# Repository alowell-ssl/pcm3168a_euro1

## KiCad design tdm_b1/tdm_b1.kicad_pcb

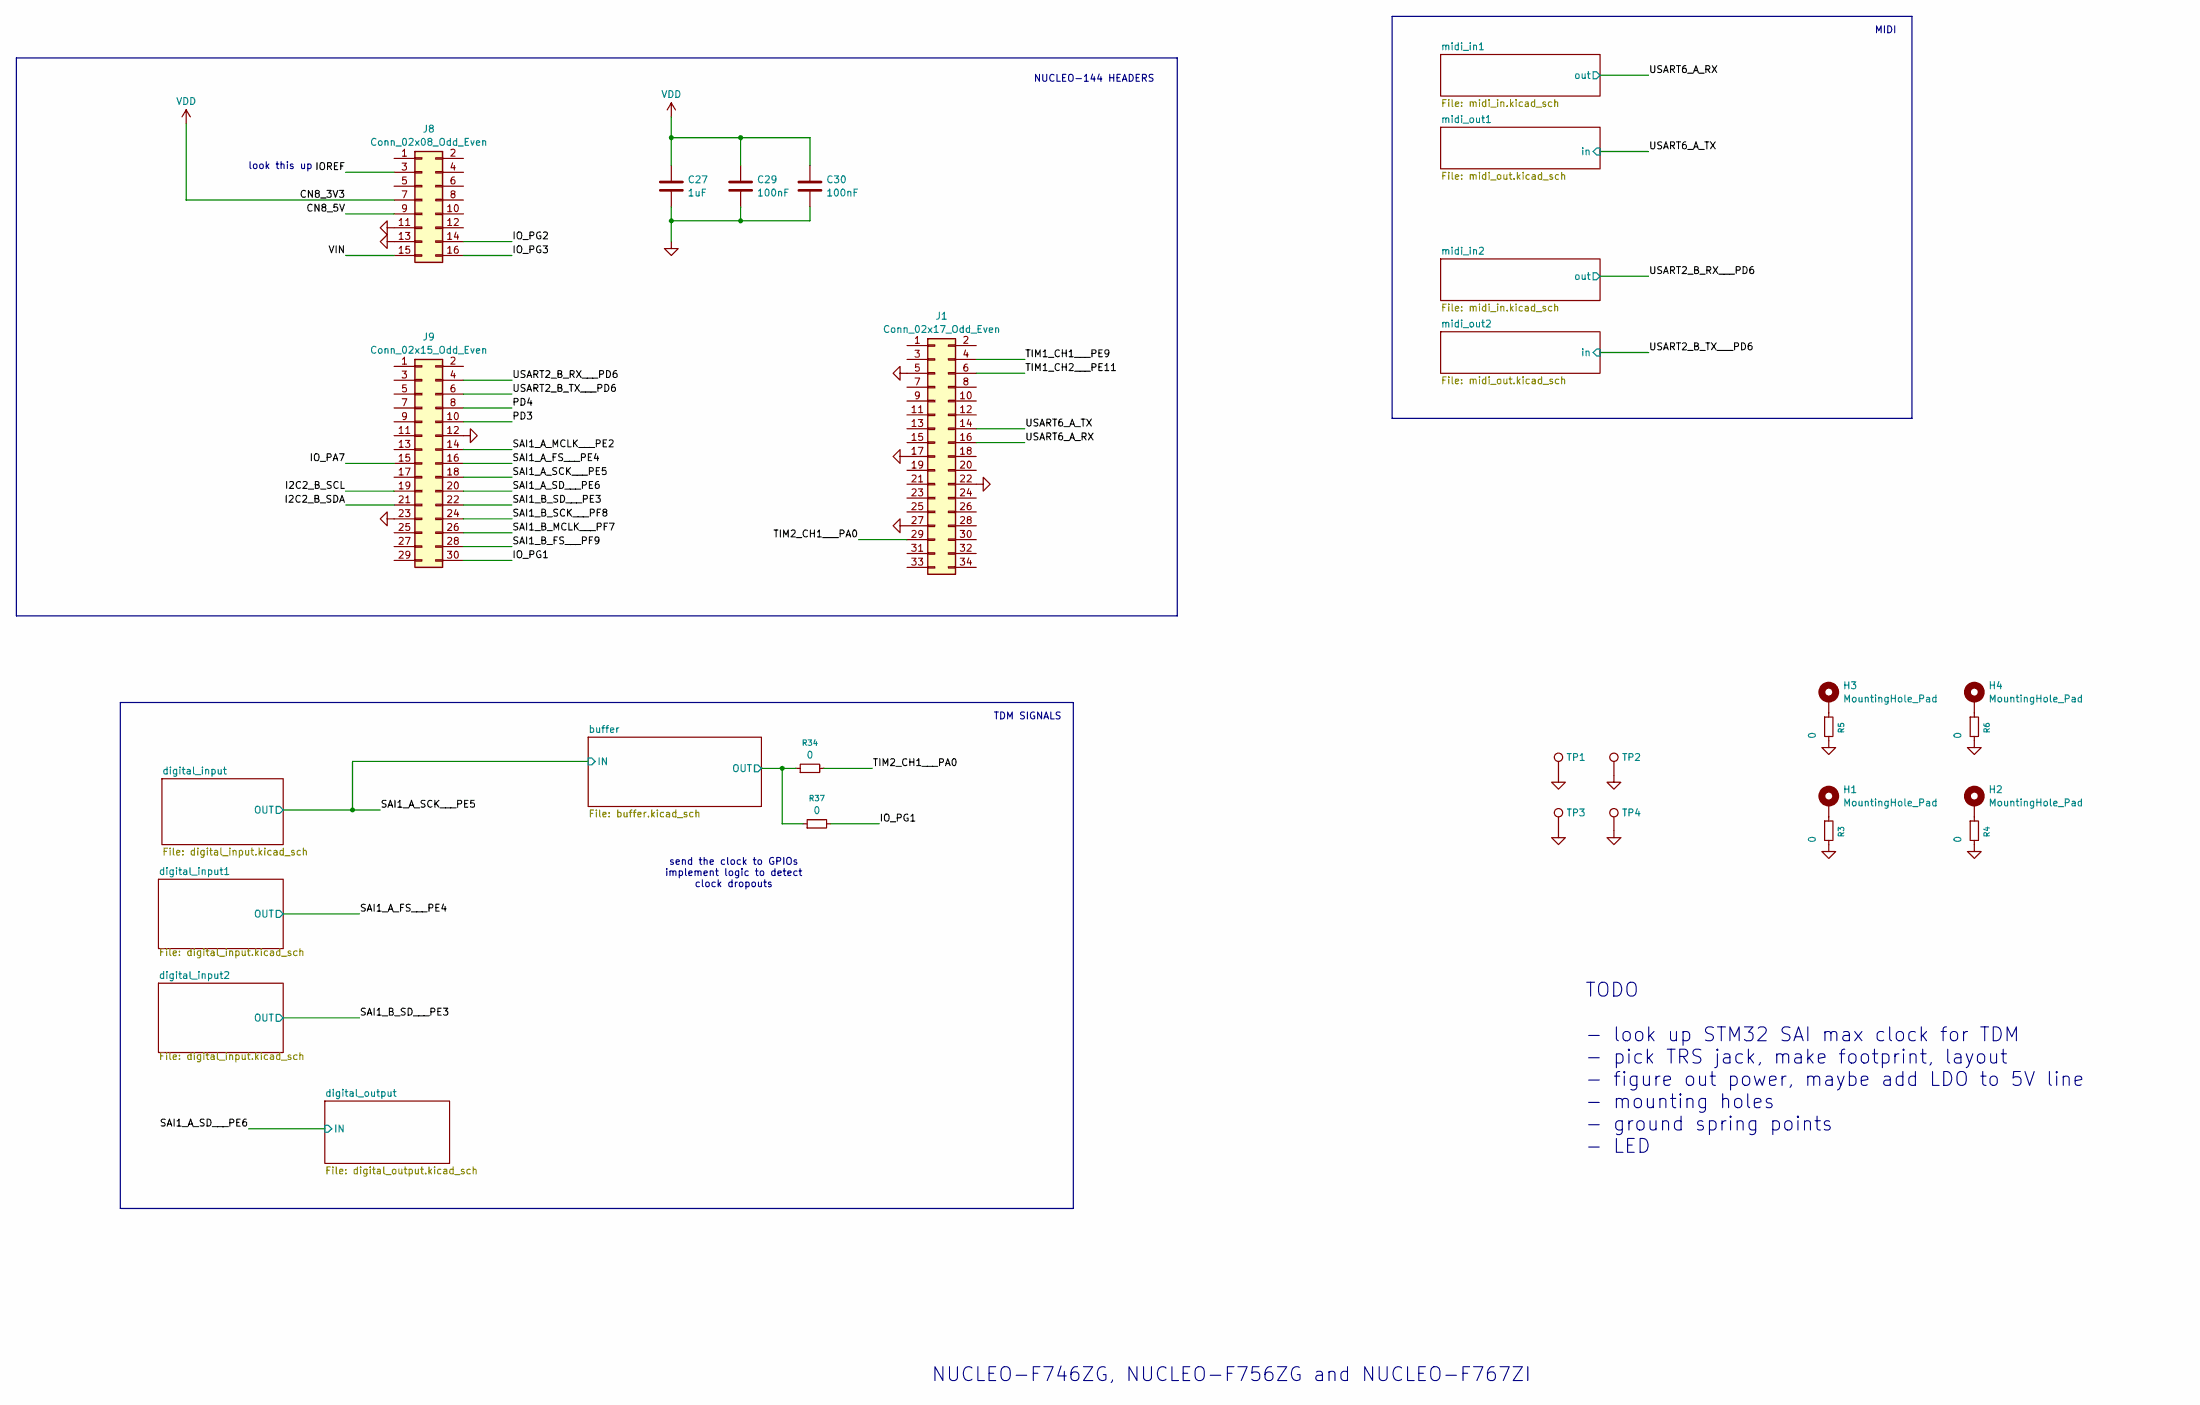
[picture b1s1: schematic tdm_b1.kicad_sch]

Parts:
C27: 1uF; C_0603_1608Metric
C29, C30: 100nF; C_0603_1608Metric
H1, H2, H3, H4: MountingHole_Pad; MountingHole_3.2mm_M3_DIN965_Pad
J1: Conn_02x17_Odd_Even; PinHeader_2x17_P2.54mm_Vertical
J8: Conn_02x08_Odd_Even; PinHeader_2x08_P2.54mm_Vertical
J9: Conn_02x15_Odd_Even; PinHeader_2x15_P2.54mm_Vertical
R3, R4, R5, R6, R34, R37: 0; R_0603_1608Metric
TP1, TP2, TP3, TP4: TestPoint; TestPoint_THTPad_D1.5mm_Drill0.7mm

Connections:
/CN8_5V: J8.9
/I2C2_B_SCL: J9.19
/I2C2_B_SDA: J9.21
/IOREF: J8.3
/IO_PA7: J9.15
/IO_PG1: J9.30, R37.2
/IO_PG2: J8.14
/IO_PG3: J8.16
/PD3: J9.10
/PD4: J9.8
/SAI1_A_FS___PE4: J9.16; also elsewhere on the board
/SAI1_A_MCLK___PE2: J9.14
/SAI1_A_SCK___PE5: J9.18; also elsewhere on the board
/SAI1_A_SD___PE6: J9.20; also elsewhere on the board
/SAI1_B_FS___PF9: J9.28
/SAI1_B_MCLK___PF7: J9.26
/SAI1_B_SCK___PF8: J9.24
/SAI1_B_SD___PE3: J9.22; also elsewhere on the board
/TIM1_CH1___PE9: J1.4
/TIM1_CH2___PE11: J1.6
/TIM2_CH1___PA0: J1.29, R34.2
/USART2_B_RX___PD6: J9.4; also elsewhere on the board
/USART2_B_TX___PD6: J9.6; also elsewhere on the board
/USART6_A_RX: J1.16; also elsewhere on the board
/USART6_A_TX: J1.14; also elsewhere on the board
/VIN: J8.15
/buffer/OUT: R34.1, R37.1; also elsewhere on the board
GND: C27.2, C29.2, C30.2, J1.5, J1.17, J1.22, J1.27, J8.11, J8.13, J9.12, J9.23, R3.2, R4.2, R5.2, R6.2, TP1.1, TP2.1, TP3.1, TP4.1; also elsewhere on the board
unnamed: H1.1, R3.1
unnamed: H2.1, R4.1
unnamed: H3.1, R5.1
unnamed: H4.1, R6.1
VDD: C27.1, C29.1, C30.1, J8.7; also elsewhere on the board

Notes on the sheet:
TDM SIGNALS
TODO - look up STM32 SAI max clock for TDM - pick TRS jack, make footprint, layout - figure out power, maybe add LDO to 5V line - mounting holes - ground spring points - LED
NUCLEO-144 HEADERS
look this up
send the clock to GPIOs implement logic to detect clock dropouts
NUCLEO-F746ZG, NUCLEO-F756ZG and NUCLEO-F767ZI
MIDI

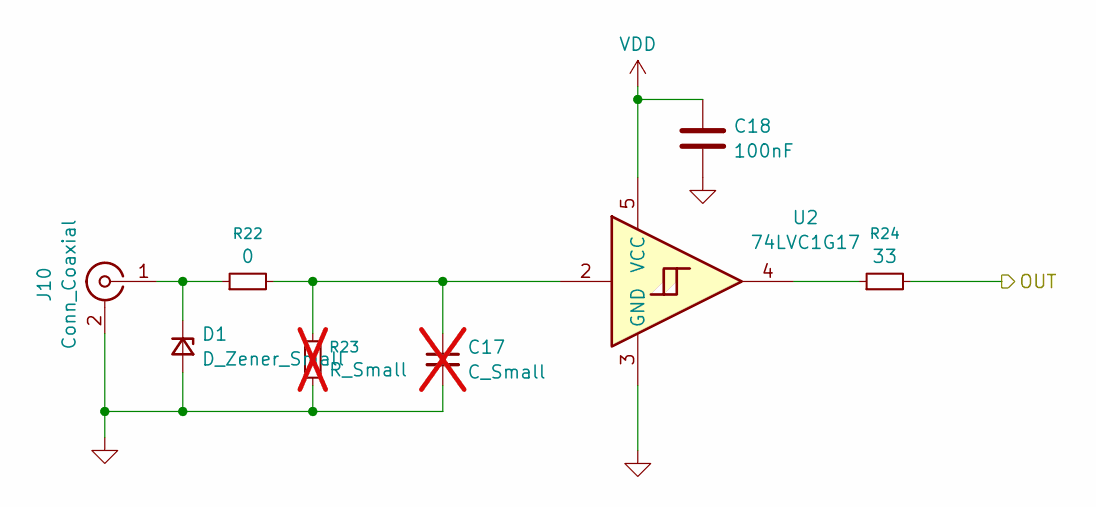
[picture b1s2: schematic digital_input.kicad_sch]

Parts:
C17: C_Small; C_0603_1608Metric; not fitted
C18: 100nF; C_0603_1608Metric
D1: D_Zener_Small; D_SOD-123F
J10: Conn_Coaxial; SMA_Amphenol_901-144_Vertical
R22: 0; R_0603_1608Metric
R23: R_Small; R_0603_1608Metric; not fitted
R24: 33; R_0603_1608Metric
U2: 74LVC1G17; SOT-23-5

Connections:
/SAI1_A_SCK___PE5: R24.2; also elsewhere on the board
GND: C17.2, C18.2, D1.2 (A), J10.2 (Ext), R23.1, U2.3 (GND); also elsewhere on the board
unnamed: C17.1, R22.2, R23.2, U2.2
unnamed: D1.1 (K), J10.1 (In), R22.1
unnamed: R24.1, U2.4
VDD: C18.1, U2.5 (VCC); also elsewhere on the board

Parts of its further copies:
C19, C21: C_Small; C_0603_1608Metric; not fitted
C20, C22: 100nF; C_0603_1608Metric
D2, D3: D_Zener_Small; D_SOD-123F
J11, J13: Conn_Coaxial; SMA_Amphenol_901-144_Vertical
R25, R28: 0; R_0603_1608Metric
R26, R29: R_Small; R_0603_1608Metric; not fitted
R27, R30: 33; R_0603_1608Metric
U3, U4: 74LVC1G17; SOT-23-5

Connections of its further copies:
/SAI1_A_FS___PE4: R27.2; also elsewhere on the board
/SAI1_B_SD___PE3: R30.2; also elsewhere on the board
GND: C19.2, C20.2, C21.2, C22.2, D2.2 (A), D3.2 (A), J11.2 (Ext), J13.2 (Ext), R26.1, R29.1, U3.3 (GND), U4.3 (GND); also elsewhere on the board
unnamed: C19.1, R25.2, R26.2, U3.2
unnamed: C21.1, R28.2, R29.2, U4.2
unnamed: D2.1 (K), J11.1 (In), R25.1
unnamed: D3.1 (K), J13.1 (In), R28.1
unnamed: R27.1, U3.4
unnamed: R30.1, U4.4
VDD: C20.1, C22.1, U3.5 (VCC), U4.5 (VCC); also elsewhere on the board

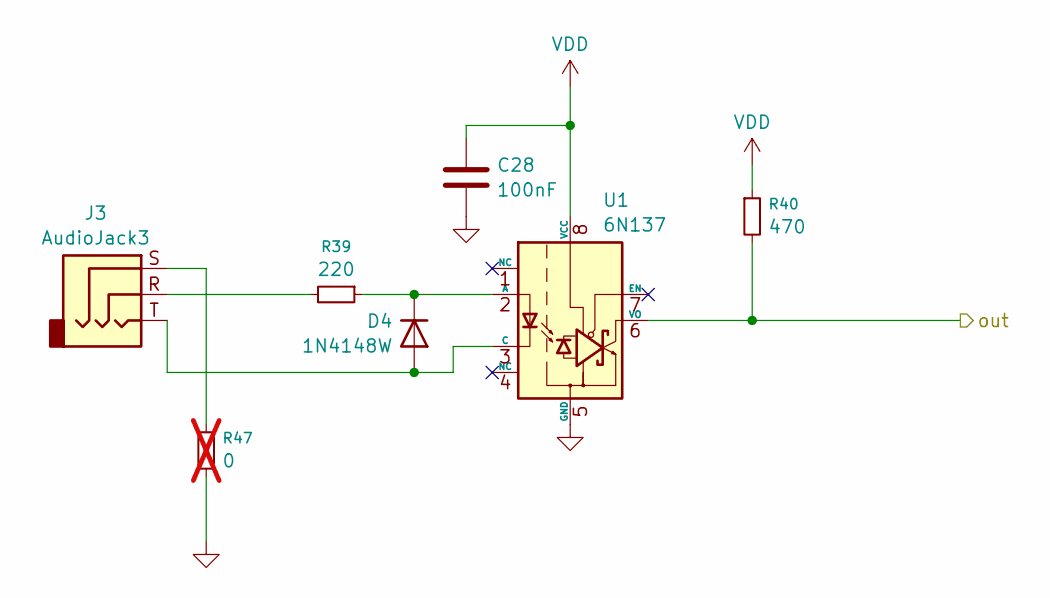
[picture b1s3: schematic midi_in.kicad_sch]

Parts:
C28: 100nF; C_0603_1608Metric
D4: 1N4148W; D_SOD-123
J3: AudioJack3; SJ1-3523N
R39: 220; R_0603_1608Metric
R40: 470; R_0603_1608Metric
R47: 0; R_0603_1608Metric; not fitted
U1: 6N137; DIP-8_W7.62mm

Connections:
/USART6_A_RX: R40.2, U1.6 (VO); also elsewhere on the board
GND: C28.2, R47.1, U1.5 (GND); also elsewhere on the board
unnamed: D4.2 (A), J3.T, U1.3 (C)
unnamed: D4.1 (K), R39.1, U1.2 (A)
unnamed: J3.R, R39.2
unnamed: J3.S, R47.2
VDD: C28.1, R40.1, U1.8 (VCC); also elsewhere on the board

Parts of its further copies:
C33: 100nF; C_0603_1608Metric
D5: 1N4148W; D_SOD-123
J5: AudioJack3; SJ1-3523N
R44: 220; R_0603_1608Metric
R45: 470; R_0603_1608Metric
R50: 0; R_0603_1608Metric; not fitted
U8: 6N137; DIP-8_W7.62mm

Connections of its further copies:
/USART2_B_RX___PD6: R45.2, U8.6 (VO); also elsewhere on the board
GND: C33.2, R50.1, U8.5 (GND); also elsewhere on the board
unnamed: D5.2 (A), J5.T, U8.3 (C)
unnamed: D5.1 (K), R44.1, U8.2 (A)
unnamed: J5.R, R44.2
unnamed: J5.S, R50.2
VDD: C33.1, R45.1, U8.8 (VCC); also elsewhere on the board

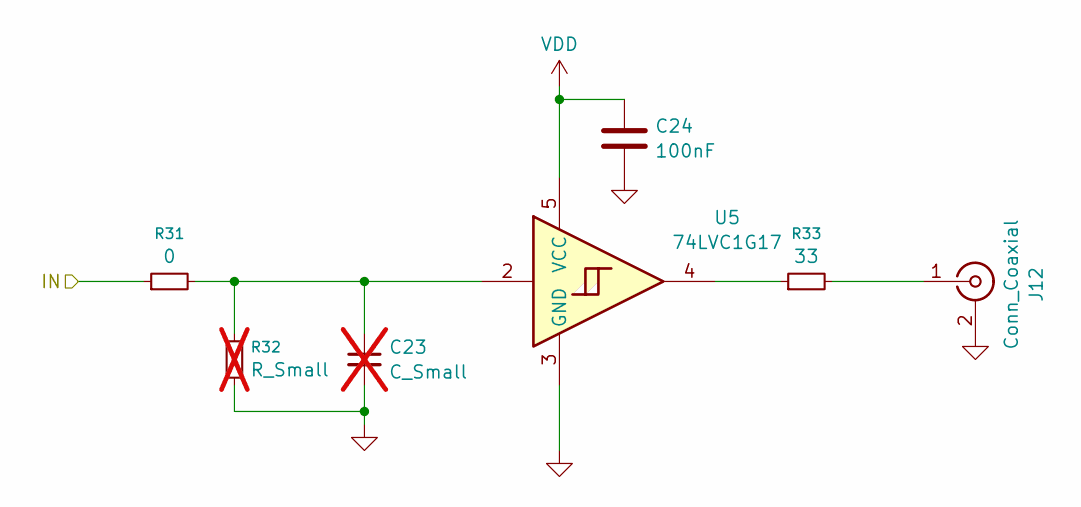
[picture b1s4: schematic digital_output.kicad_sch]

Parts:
C23: C_Small; C_0603_1608Metric; not fitted
C24: 100nF; C_0603_1608Metric
J12: Conn_Coaxial; SMA_Amphenol_901-144_Vertical
R31: 0; R_0603_1608Metric
R32: R_Small; R_0603_1608Metric; not fitted
R33: 33; R_0603_1608Metric
U5: 74LVC1G17; SOT-23-5

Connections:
/SAI1_A_SD___PE6: R31.1; also elsewhere on the board
GND: C23.2, C24.2, J12.2 (Ext), R32.1, U5.3 (GND); also elsewhere on the board
unnamed: C23.1, R31.2, R32.2, U5.2
unnamed: J12.1 (In), R33.2
unnamed: R33.1, U5.4
VDD: C24.1, U5.5 (VCC); also elsewhere on the board

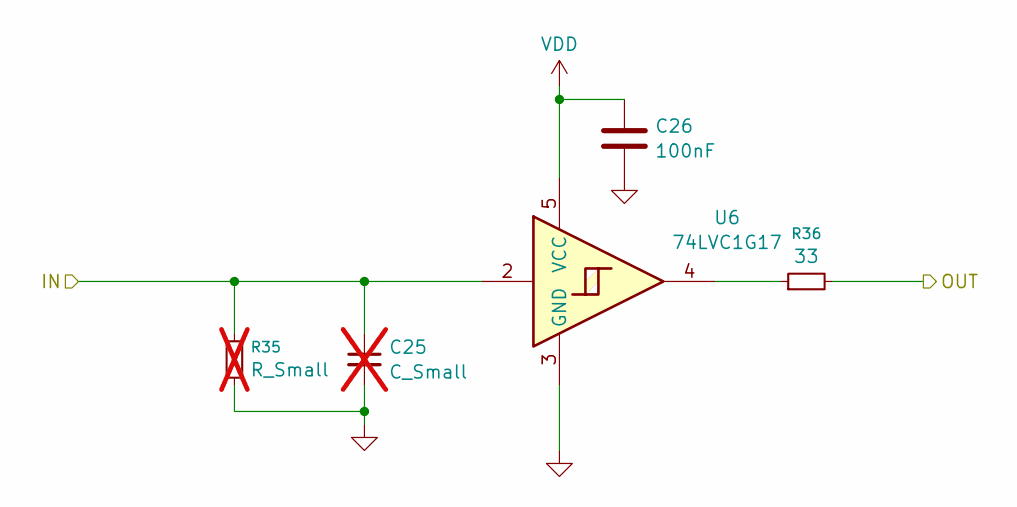
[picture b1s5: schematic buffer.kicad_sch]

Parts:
C25: C_Small; C_0603_1608Metric; not fitted
C26: 100nF; C_0603_1608Metric
R35: R_Small; R_0603_1608Metric; not fitted
R36: 33; R_0603_1608Metric
U6: 74LVC1G17; SOT-23-5

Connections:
/SAI1_A_SCK___PE5: C25.1, R35.2, U6.2; also elsewhere on the board
/buffer/OUT: R36.2; also elsewhere on the board
GND: C25.2, C26.2, R35.1, U6.3 (GND); also elsewhere on the board
unnamed: R36.1, U6.4
VDD: C26.1, U6.5 (VCC); also elsewhere on the board

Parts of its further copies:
C31, C34: C_Small; C_0603_1608Metric; not fitted
C32, C35: 100nF; C_0603_1608Metric
R41, R46: R_Small; R_0603_1608Metric; not fitted
R42, R51: 33; R_0603_1608Metric
U7, U9: 74LVC1G17; SOT-23-5

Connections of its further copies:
/USART2_B_TX___PD6: C34.1, R46.2, U9.2; also elsewhere on the board
/USART6_A_TX: C31.1, R41.2, U7.2; also elsewhere on the board
/midi_out1/MIDI_OUT: R42.2; also elsewhere on the board
/midi_out2/MIDI_OUT: R51.2; also elsewhere on the board
GND: C31.2, C32.2, C34.2, C35.2, R41.1, R46.1, U7.3 (GND), U9.3 (GND); also elsewhere on the board
unnamed: R42.1, U7.4
unnamed: R51.1, U9.4
VDD: C32.1, C35.1, U7.5 (VCC), U9.5 (VCC); also elsewhere on the board

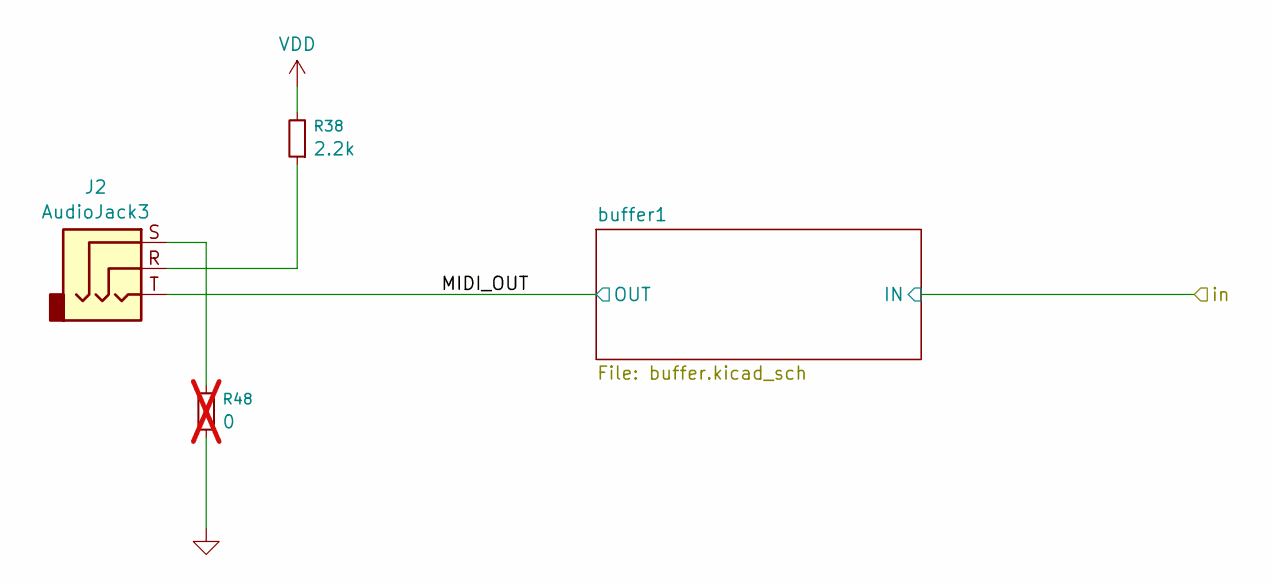
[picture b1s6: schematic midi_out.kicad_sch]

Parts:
J2: AudioJack3; SJ1-3523N
R38: 2.2k; R_0603_1608Metric
R48: 0; R_0603_1608Metric; not fitted

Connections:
/midi_out1/MIDI_OUT: J2.T; also elsewhere on the board
GND: R48.1; also elsewhere on the board
unnamed: J2.R, R38.1
unnamed: J2.S, R48.2
VDD: R38.2; also elsewhere on the board

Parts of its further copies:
J4: AudioJack3; SJ1-3523N
R43: 2.2k; R_0603_1608Metric
R49: 0; R_0603_1608Metric; not fitted

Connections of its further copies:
/midi_out2/MIDI_OUT: J4.T; also elsewhere on the board
GND: R49.1; also elsewhere on the board
unnamed: J4.R, R43.1
unnamed: J4.S, R49.2
VDD: R43.2; also elsewhere on the board

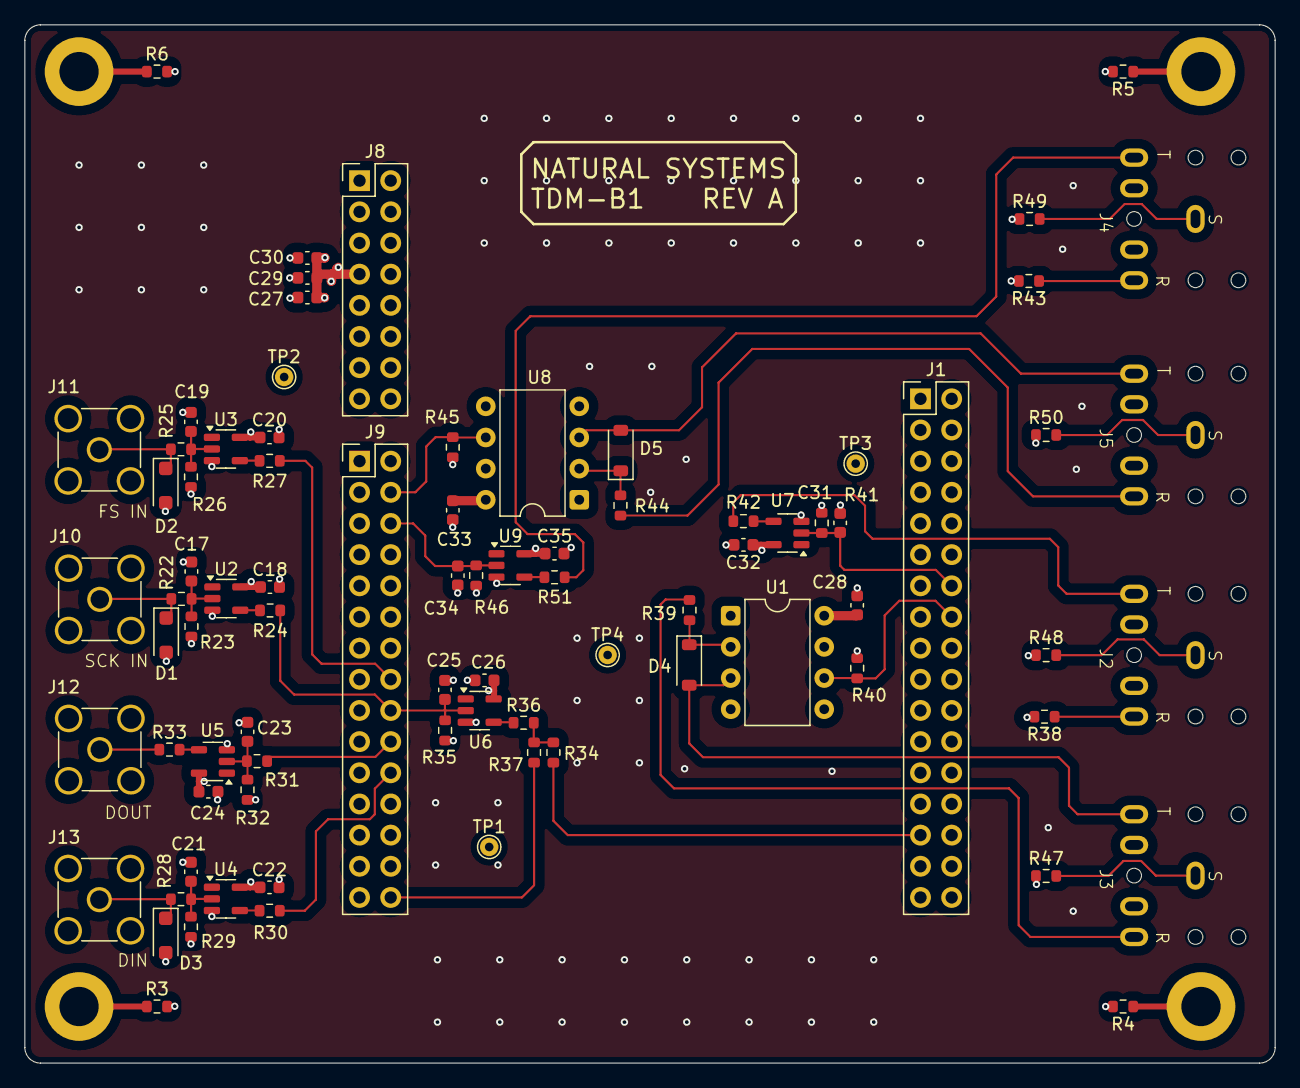
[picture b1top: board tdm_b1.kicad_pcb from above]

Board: 4 copper layers, 101.9 x 84.6 mm, 86 parts (0 on the bottom side), 46 nets.

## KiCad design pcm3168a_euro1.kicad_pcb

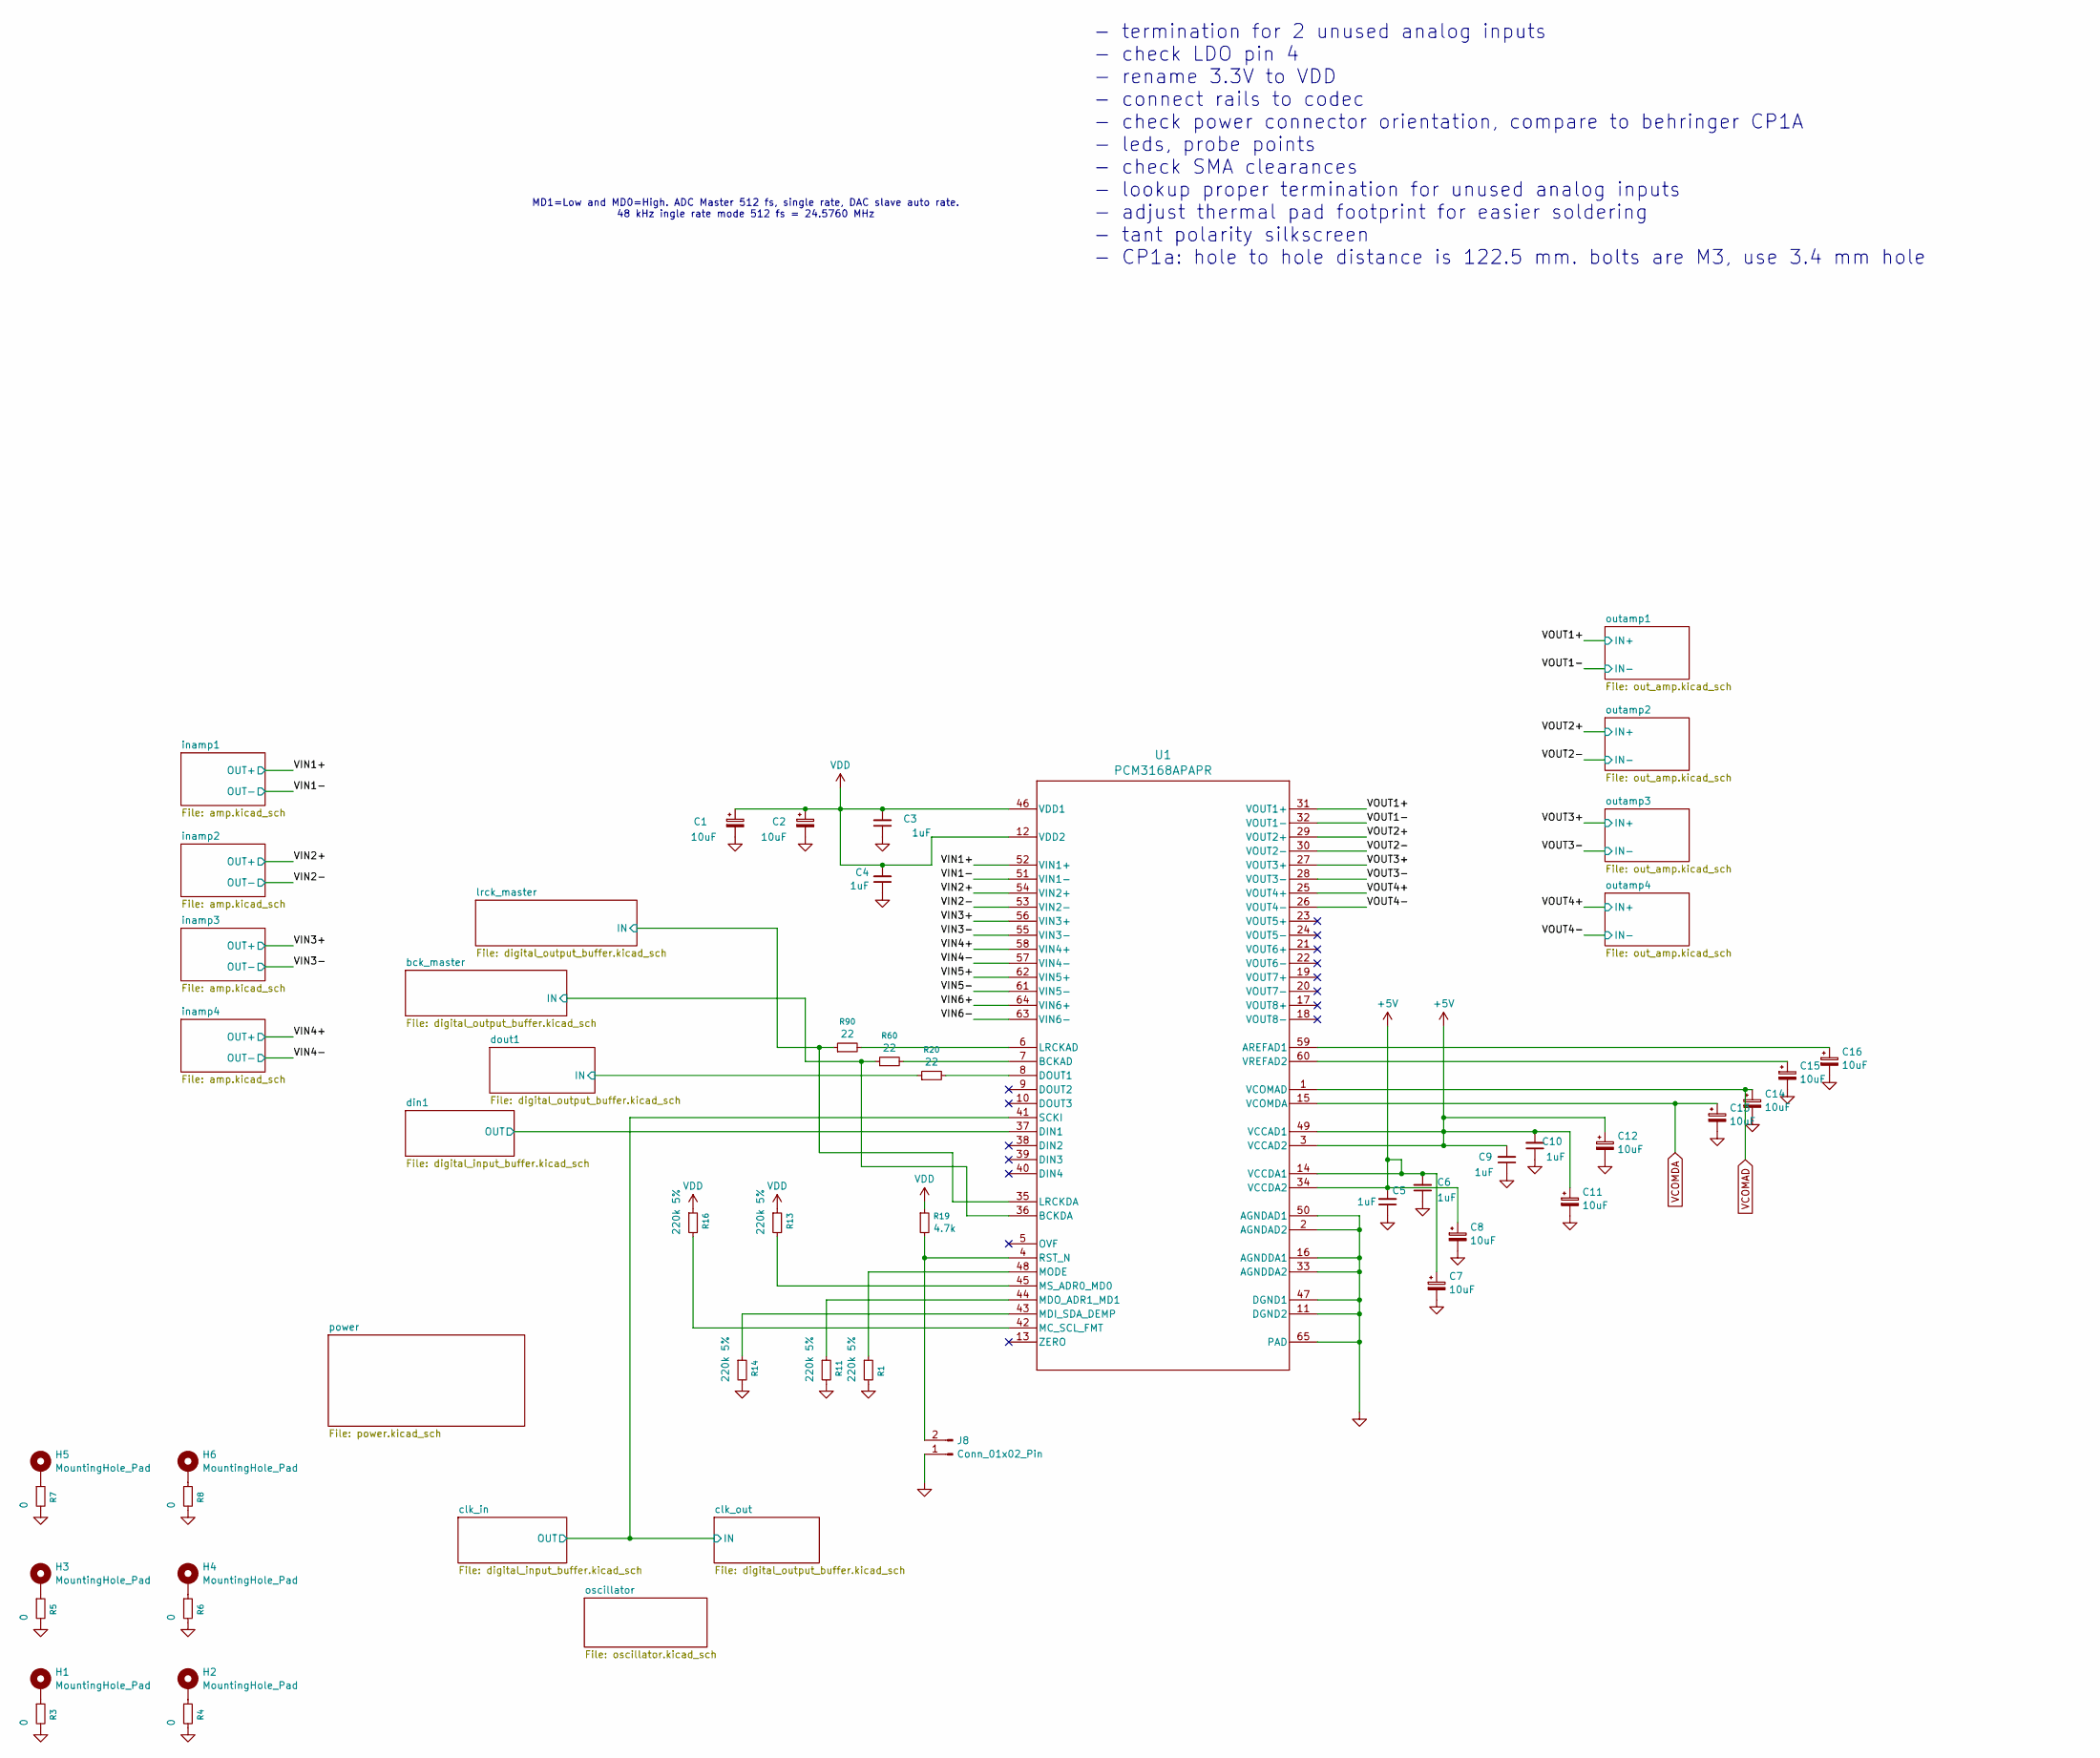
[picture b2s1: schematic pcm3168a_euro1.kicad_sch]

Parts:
C1, C2, C7, C8, C11, C12, C13, C14, C15, C16: 10uF; C_1206_3216Metric
C3, C4, C5, C6, C9, C10: 1uF; C_0603_1608Metric
H1, H2, H3, H4, H5, H6: MountingHole_Pad; MountingHole_3.2mm_M3_DIN965_Pad
J8: Conn_01x02_Pin; PinHeader_1x02_P2.54mm_Vertical
R1, R11, R13, R14, R16: 220k 5%; R_0603_1608Metric
R3, R4, R5, R6, R7, R8: 0; R_0603_1608Metric
R19: 4.7k; R_0603_1608Metric
R20, R60, R90: 22; R_0603_1608Metric
U1: PCM3168APAPR; PAP0064J_M

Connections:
+5V: C5.2, C6.2, C7.1, C8.1, C9.2, C10.2, C11.1, C12.1, U1.3 (VCCAD2), U1.14 (VCCDA1), U1.34 (VCCDA2), U1.49 (VCCAD1); also elsewhere on the board
/VIN1+: U1.52 (VIN1+); also elsewhere on the board
/VIN1-: U1.51 (VIN1-); also elsewhere on the board
/VIN2+: U1.54 (VIN2+); also elsewhere on the board
/VIN2-: U1.53 (VIN2-); also elsewhere on the board
/VIN3+: U1.56 (VIN3+); also elsewhere on the board
/VIN3-: U1.55 (VIN3-); also elsewhere on the board
/VIN4+: U1.58 (VIN4+); also elsewhere on the board
/VIN4-: U1.57 (VIN4-); also elsewhere on the board
/VIN5+: U1.62 (VIN5+)
/VIN5-: U1.61 (VIN5-)
/VIN6+: U1.64 (VIN6+)
/VIN6-: U1.63 (VIN6-)
/VOUT1+: U1.31 (VOUT1+); also elsewhere on the board
/VOUT1-: U1.32 (VOUT1-); also elsewhere on the board
/VOUT2+: U1.29 (VOUT2+); also elsewhere on the board
/VOUT2-: U1.30 (VOUT2-); also elsewhere on the board
/VOUT3+: U1.27 (VOUT3+); also elsewhere on the board
/VOUT3-: U1.28 (VOUT3-); also elsewhere on the board
/VOUT4+: U1.25 (VOUT4+); also elsewhere on the board
/VOUT4-: U1.26 (VOUT4-); also elsewhere on the board
/bck_master/IN: R60.1, U1.36 (BCKDA); also elsewhere on the board
/clk_in/OUT: U1.41 (SCKI); also elsewhere on the board
/din1/OUT: U1.37 (DIN1); also elsewhere on the board
/dout1/IN: R20.1; also elsewhere on the board
/lrck_master/IN: R90.1, U1.35 (LRCKDA); also elsewhere on the board
GND: C1.2, C2.2, C3.1, C4.1, C5.1, C6.1, C7.2, C8.2, C9.1, C10.1, C11.2, C12.2, C13.2, C14.2, C15.2, C16.2, J8.1, R1.2, R3.2, R4.2, R5.2, R6.2, R7.2, R8.2, R11.2, R14.2, U1.2 (AGNDAD2), U1.11 (DGND2), U1.16 (AGNDDA1), U1.33 (AGNDDA2), U1.47 (DGND1), U1.50 (AGNDAD1), U1.65 (PAD); also elsewhere on the board
unnamed: H1.1, R3.1
unnamed: H2.1, R4.1
unnamed: H3.1, R5.1
unnamed: H4.1, R6.1
unnamed: H5.1, R7.1
unnamed: H6.1, R8.1
unnamed: J8.2, R19.2, U1.4 (RST_N)
unnamed: C16.1, U1.59 (AREFAD1)
unnamed: R60.2, U1.7 (BCKAD)
unnamed: R20.2, U1.8 (DOUT1)
unnamed: R90.2, U1.6 (LRCKAD)
unnamed: R16.2, U1.42 (MC_SCL_FMT)
unnamed: R14.1, U1.43 (MDI_SDA_DEMP)
unnamed: R11.1, U1.44 (MDO_ADR1_MD1)
unnamed: R1.1, U1.48 (MODE)
unnamed: R13.2, U1.45 (MS_ADR0_MD0)
unnamed: C15.1, U1.60 (VREFAD2)
VCOMAD: C14.1, U1.1 (VCOMAD); also elsewhere on the board
VCOMDA: C13.1, U1.15 (VCOMDA); also elsewhere on the board
VDD: C1.1, C2.1, C3.2, C4.2, R13.1, R16.1, R19.1, U1.12 (VDD2), U1.46 (VDD1); also elsewhere on the board

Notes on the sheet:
- termination for 2 unused analog inputs - check LDO pin 4 - rename 3.3V to VDD - connect rails to codec - check power connector orientation, compare to behringer CP1A - leds, probe points - check SMA clearances - lookup proper termination for unused analog inputs - adjust thermal pad footprint for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
MD1=Low and MD0=High. ADC Master 512 fs, single rate, DAC slave auto rate. 48 kHz ingle rate mode 512 fs = 24.5760 MHz

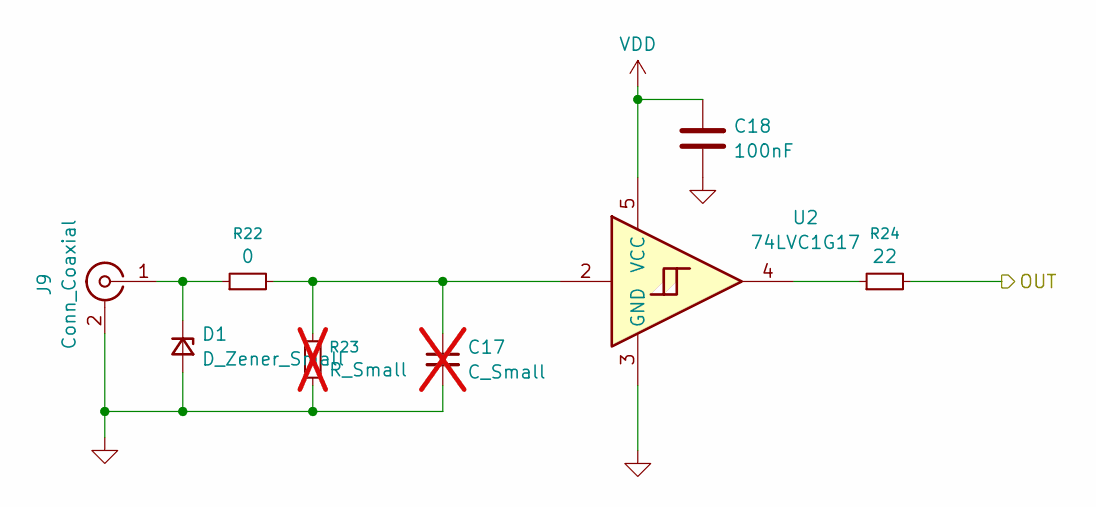
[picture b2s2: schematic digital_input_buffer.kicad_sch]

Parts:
C17: C_Small; C_0603_1608Metric; not fitted
C18: 100nF; C_0603_1608Metric
D1: D_Zener_Small; D_SOD-123F
J9: Conn_Coaxial; SMA_Amphenol_901-144_Vertical
R22: 0; R_0603_1608Metric
R23: R_Small; R_0603_1608Metric; not fitted
R24: 22; R_0603_1608Metric
U2: 74LVC1G17; SOT-23-5

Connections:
/din1/OUT: R24.2; also elsewhere on the board
GND: C17.2, C18.2, D1.2 (A), J9.2 (Ext), R23.1, U2.3 (GND); also elsewhere on the board
unnamed: C17.1, R22.2, R23.2, U2.2
unnamed: D1.1 (K), J9.1 (In), R22.1
unnamed: R24.1, U2.4
VDD: C18.1, U2.5 (VCC); also elsewhere on the board

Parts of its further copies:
C21: C_Small; C_0603_1608Metric; not fitted
C22: 100nF; C_0603_1608Metric
D2: D_Zener_Small; D_SOD-123F
J11: Conn_Coaxial; SMA_Amphenol_901-144_Vertical
R28: 0; R_0603_1608Metric
R29: R_Small; R_0603_1608Metric; not fitted
R30: 22; R_0603_1608Metric
U4: 74LVC1G17; SOT-23-5

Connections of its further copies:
/clk_in/OUT: R30.2; also elsewhere on the board
GND: C21.2, C22.2, D2.2 (A), J11.2 (Ext), R29.1, U4.3 (GND); also elsewhere on the board
unnamed: C21.1, R28.2, R29.2, U4.2
unnamed: D2.1 (K), J11.1 (In), R28.1
unnamed: R30.1, U4.4
VDD: C22.1, U4.5 (VCC); also elsewhere on the board

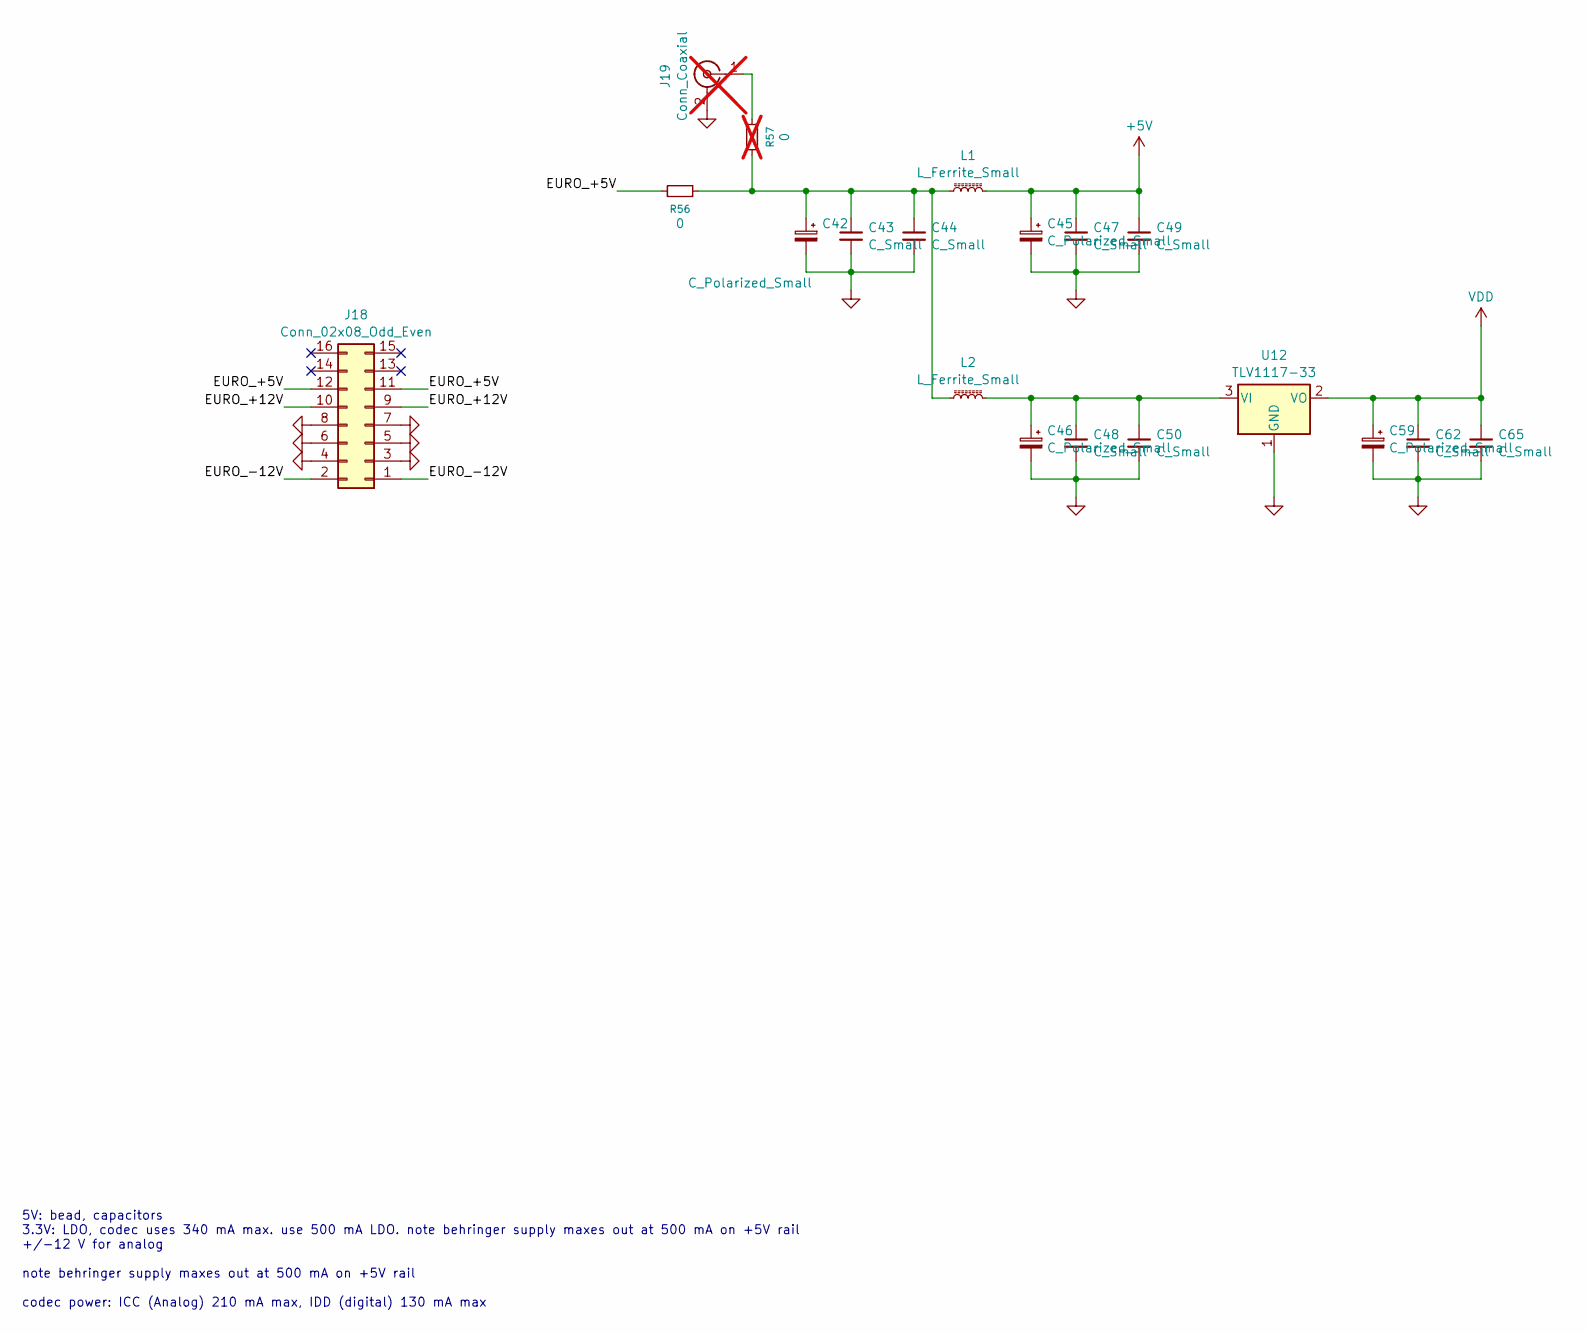
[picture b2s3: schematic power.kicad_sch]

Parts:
C42, C45, C46, C59: C_Polarized_Small; CP_Radial_D8.0mm_P3.50mm
C43, C44, C47, C48, C49, C50, C62, C65: C_Small; C_0603_1608Metric
J18: Conn_02x08_Odd_Even; PinSocket_2x08_P2.54mm_Vertical
J19: Conn_Coaxial; SMA_Amphenol_901-144_Vertical; not fitted
L1, L2: L_Ferrite_Small; L_0603_1608Metric
R56: 0; R_0603_1608Metric
R57: 0; R_0603_1608Metric; not fitted
U12: TLV1117-33; SOT-223

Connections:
+5V: C45.1, C47.1, C49.1, L1.2; also elsewhere on the board
/power/EURO_+5V: J18.11, J18.12, R56.1
/power/EURO_+12V: J18.9, J18.10
/power/EURO_-12V: J18.1, J18.2
GND: C42.2, C43.2, C44.2, C45.2, C46.2, C47.2, C48.2, C49.2, C50.2, C59.2, C62.2, C65.2, J18.3, J18.4, J18.5, J18.6, J18.7, J18.8, J19.2 (Ext), U12.1 (GND); also elsewhere on the board
unnamed: C42.1, C43.1, C44.1, L1.1, L2.1, R56.2, R57.1
unnamed: J19.1 (In), R57.2
unnamed: C46.1, C48.1, C50.1, L2.2, U12.3 (VI)
VDD: C59.1, C62.1, C65.1, U12.2 (VO); also elsewhere on the board

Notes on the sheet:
5V: bead, capacitors 3.3V: LDO, codec uses 340 mA max. use 500 mA LDO. note behringer supply maxes out at 500 mA on +5V rail +/-12 V for analog note behringer supply maxes out at 500 mA on +5V rail codec power: ICC (Analog) 210 mA max, IDD (digital) 130 mA max
